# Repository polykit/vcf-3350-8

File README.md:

# Polykit VCF-3350-8

This repository contains schematics and Kicad PCB layout for an eight channel voltage controlled filter (VCF) based on the CEM3350/AS3350 state variable filter. Both frequency cutoff and resonance (Q) are voltage controllable. It offers a simoultaneous low-pass and band-pass output.

## References

https://electricdruid.net/datasheets/AS3350.pdf

http://www.synfo.nl/datasheets/CEM3350.pdf

http://www.electricdruid.net/datasheets/EMEngCEM3350.pdf

https://archive.org/details/sm_Synthesource_Issue_2

http://www.digisound80.co.uk/digisound/modules/80-16.htm

https://kg.kg/cem3350-eurorack-filter/

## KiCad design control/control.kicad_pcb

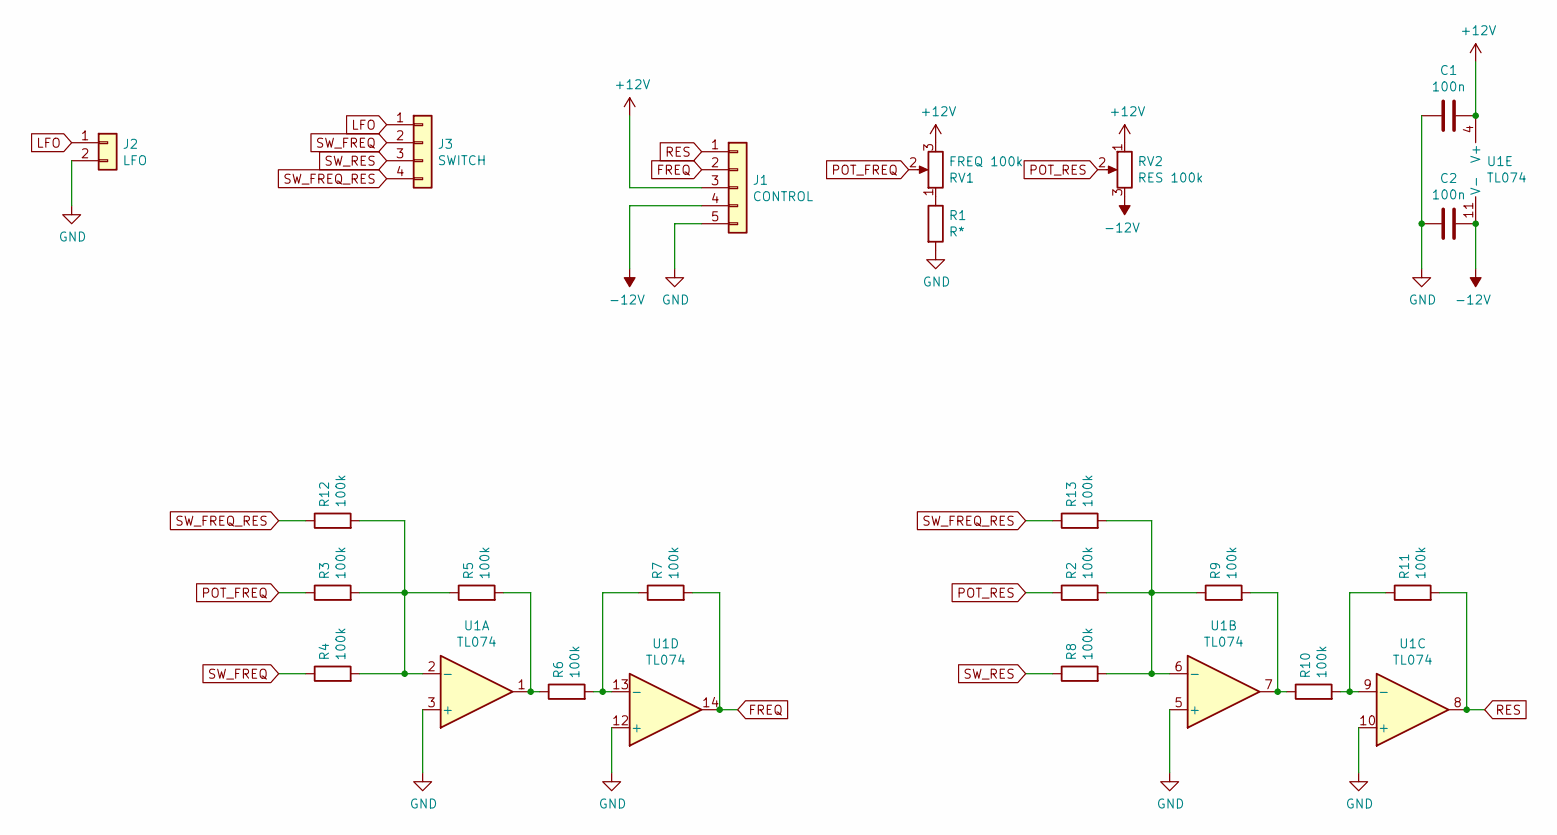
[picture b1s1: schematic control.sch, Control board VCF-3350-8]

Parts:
C1, C2: 100n; C_Disc_D3.0mm_W2.0mm_P2.50mm
J1: CONTROL; Molex_KK-254_AE-6410-05A_1x05_P2.54mm_Vertical
J2: LFO; Molex_KK-254_AE-6410-02A_1x02_P2.54mm_Vertical
J3: SWITCH; Molex_KK-254_AE-6410-04A_1x04_P2.54mm_Vertical
R1: R*; R_Axial_DIN0207_L6.3mm_D2.5mm_P10.16mm_Horizontal
R2, R3, R4, R5, R6, R7, R8, R9, R10, R11, R12, R13: 100k; R_Axial_DIN0207_L6.3mm_D2.5mm_P10.16mm_Horizontal
RV1: FREQ 100k; Potentiometer_Alpha_RD901F-40-00D_Single_Vertical
RV2: RES 100k; Potentiometer_Alpha_RD901F-40-00D_Single_Vertical
U1: TL074; DIP-14_W7.62mm_Socket_LongPads

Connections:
+12V: C1.2, J1.3, RV1.3, RV2.1, U1.4 (V+)
-12V: C2.2, J1.4, RV2.3, U1.11 (V-)
FREQ: J1.2, R7.2, U1.14
GND: C1.1, C2.1, J1.5, J2.2, R1.2, U1.3 (+), U1.5 (+), U1.10 (+), U1.12 (+)
LFO: J2.1, J3.1
unnamed: R1.1, RV1.1
unnamed: R5.2, R6.1, U1.1
unnamed: R6.2, R7.1, U1.13 (-)
unnamed: R9.2, R10.1, U1.7
unnamed: R10.2, R11.1, U1.9 (-)
unnamed: R3.2, R4.2, R5.1, R12.2, U1.2 (-)
unnamed: R2.2, R8.2, R9.1, R13.2, U1.6 (-)
POT_FREQ: R3.1, RV1.2
POT_RES: R2.1, RV2.2
RES: J1.1, R11.2, U1.8
SW_FREQ: J3.2, R4.1
SW_FREQ_RES: J3.4, R12.1, R13.1
SW_RES: J3.3, R8.1

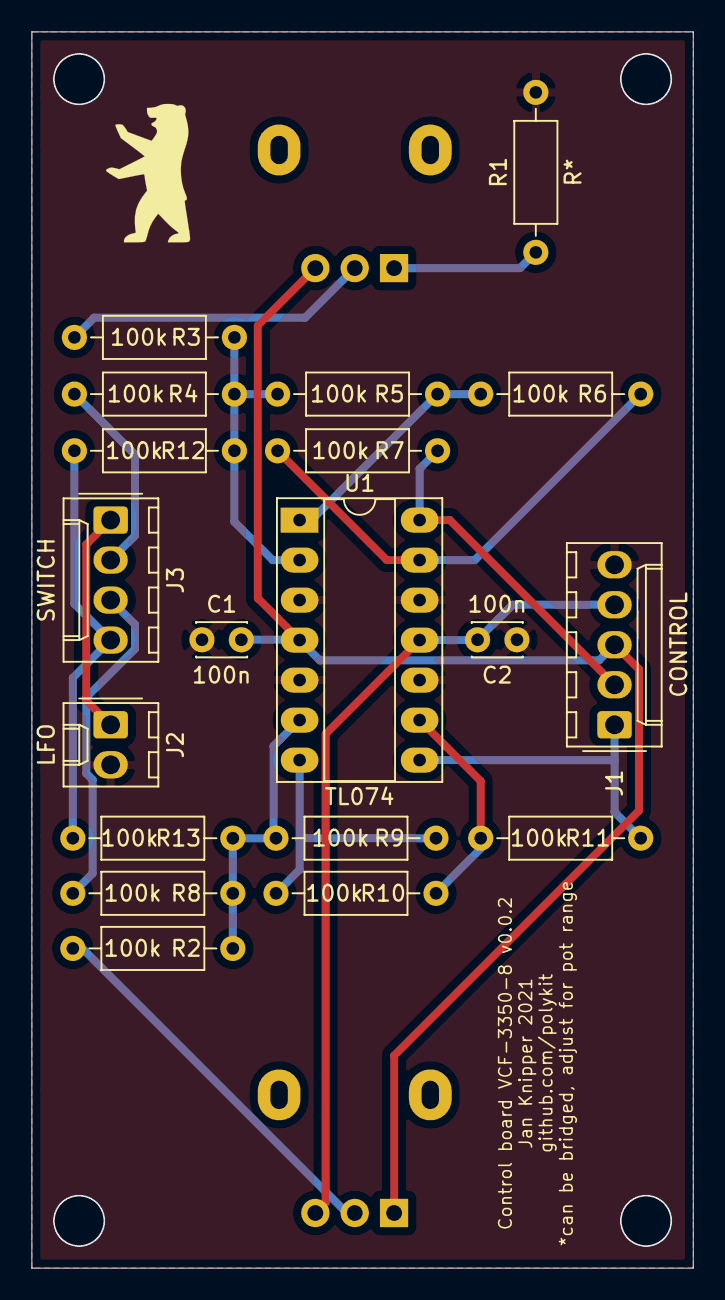
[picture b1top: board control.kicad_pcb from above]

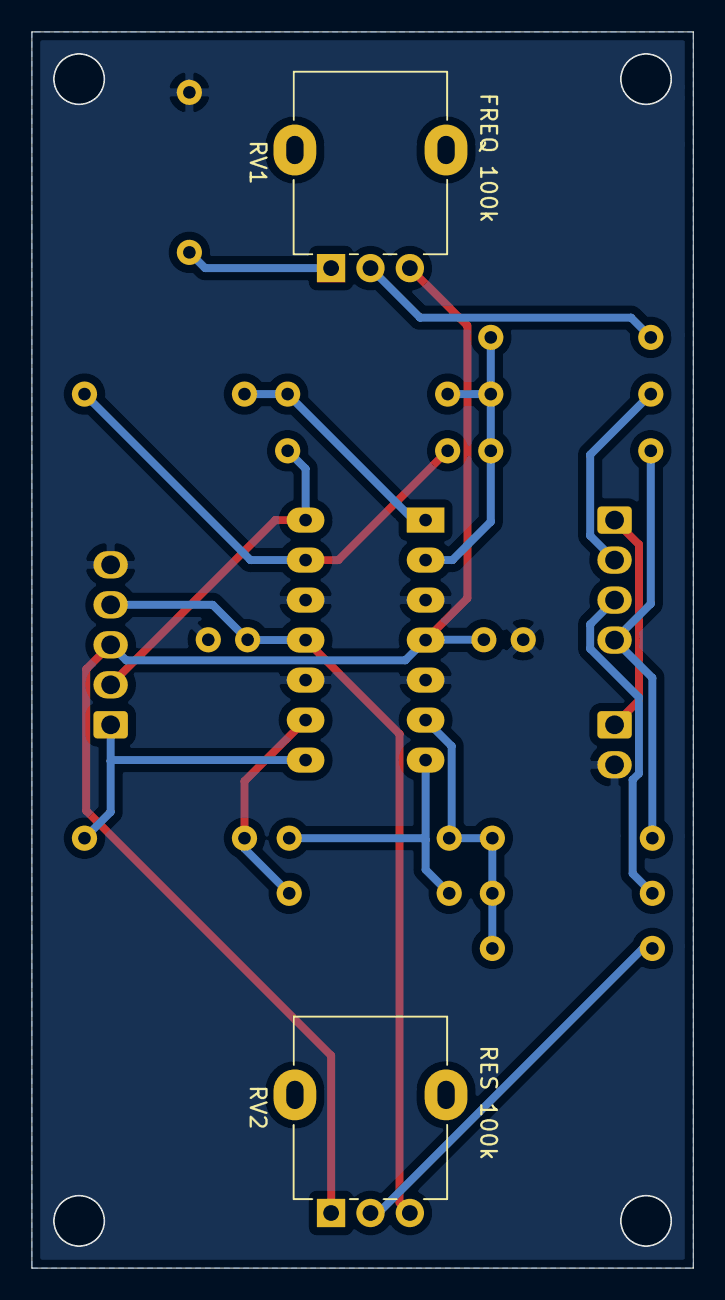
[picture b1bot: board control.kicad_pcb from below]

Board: 2 copper layers, 42.0 x 78.5 mm, 21 parts (2 on the bottom side), 18 nets.

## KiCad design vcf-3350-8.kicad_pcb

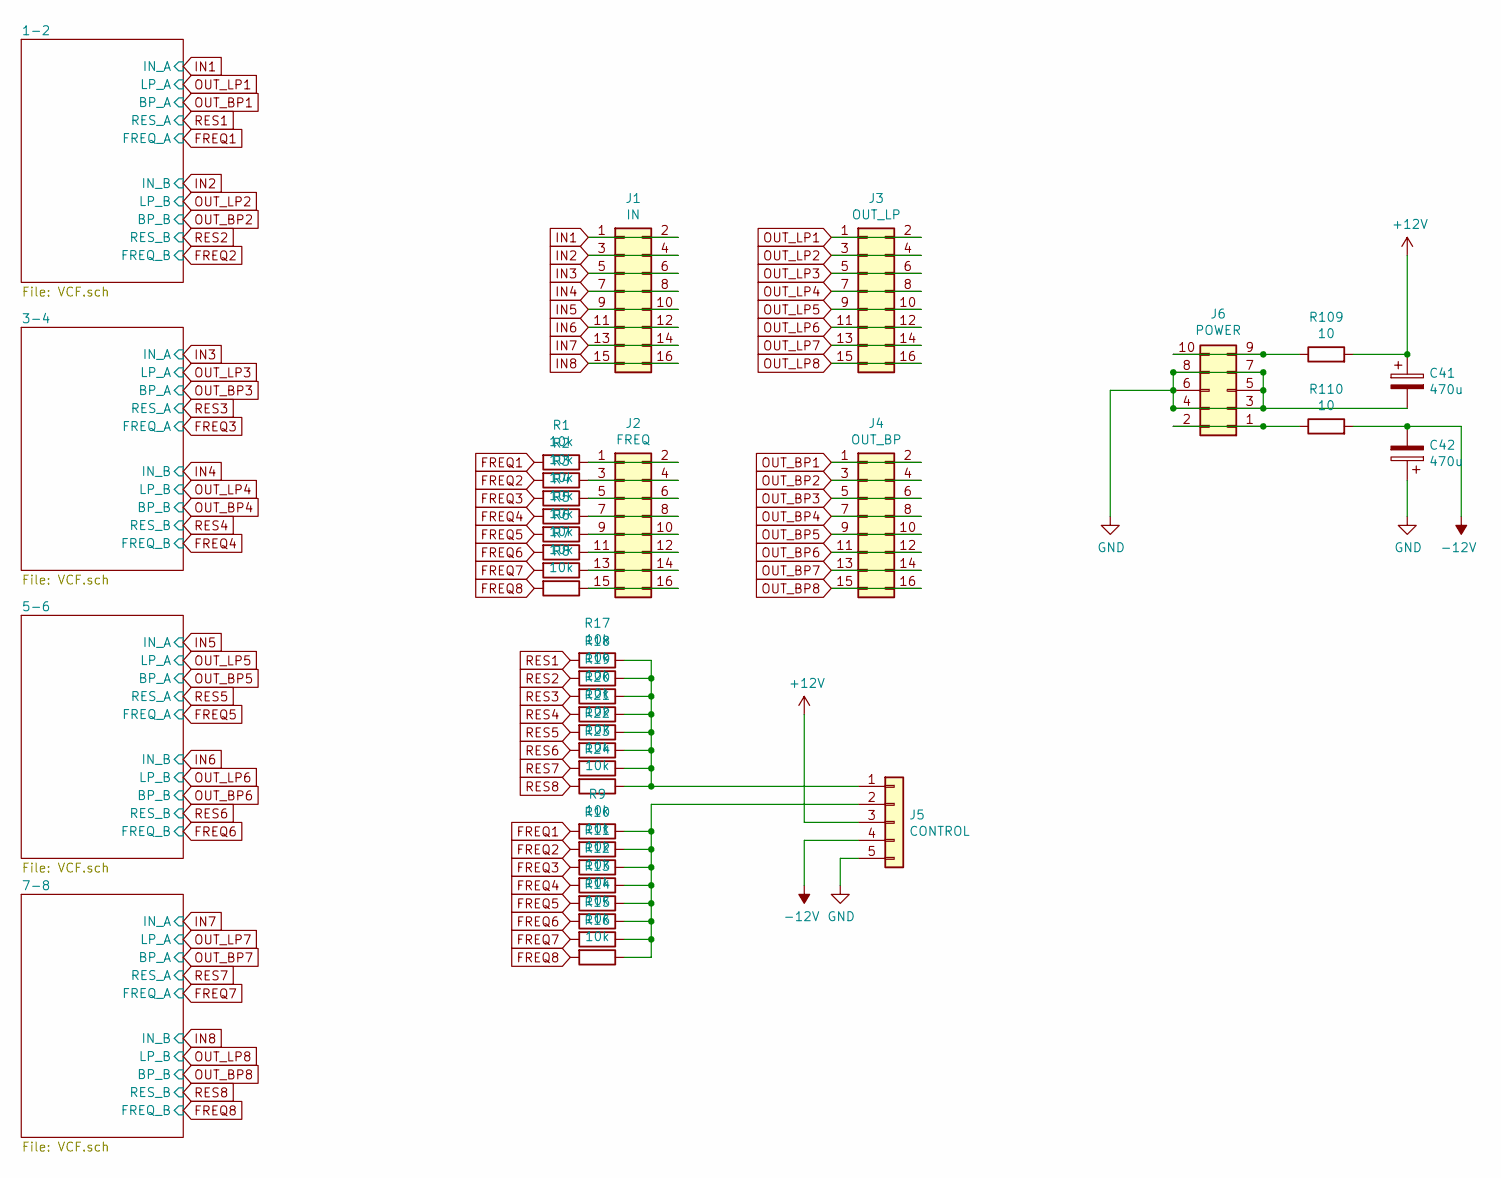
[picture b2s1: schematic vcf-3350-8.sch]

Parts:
C41, C42: 470u; CP_Radial_D8.0mm_P5.00mm
J1: IN; IDC-Header_2x08_P2.54mm_Vertical
J2: FREQ; IDC-Header_2x08_P2.54mm_Vertical
J3: OUT_LP; IDC-Header_2x08_P2.54mm_Vertical
J4: OUT_BP; IDC-Header_2x08_P2.54mm_Vertical
J5: CONTROL; Molex_KK-254_AE-6410-05A_1x05_P2.54mm_Vertical
J6: POWER; IDC-Header_2x05_P2.54mm_Vertical
R1, R2, R3, R4, R5, R6, R7, R8, R9, R10, R11, R12, R13, R14, R15, R16, R17, R18, R19, R20, R21, R22, R23, R24: 10k; R_Axial_DIN0204_L3.6mm_D1.6mm_P2.54mm_Vertical
R109, R110: 10; R_Axial_DIN0207_L6.3mm_D2.5mm_P10.16mm_Horizontal

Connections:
+12V: C41.1, J5.3, R109.2; also elsewhere on the board
-12V: C42.2, J5.4, R110.2; also elsewhere on the board
FREQ1: R1.2, R9.2; also elsewhere on the board
FREQ2: R2.2, R10.2; also elsewhere on the board
FREQ3: R3.2, R11.2; also elsewhere on the board
FREQ4: R4.2, R12.2; also elsewhere on the board
FREQ5: R5.2, R13.2; also elsewhere on the board
FREQ6: R6.2, R14.2; also elsewhere on the board
FREQ7: R7.2, R15.2; also elsewhere on the board
FREQ8: R8.2, R16.2; also elsewhere on the board
GND: C41.2, C42.1, J5.5, J6.3, J6.4, J6.5, J6.6, J6.7, J6.8; also elsewhere on the board
IN1: J1.1, J1.2; also elsewhere on the board
IN2: J1.3, J1.4; also elsewhere on the board
IN3: J1.5, J1.6; also elsewhere on the board
IN4: J1.7, J1.8; also elsewhere on the board
IN5: J1.9, J1.10; also elsewhere on the board
IN6: J1.11, J1.12; also elsewhere on the board
IN7: J1.13, J1.14; also elsewhere on the board
IN8: J1.15, J1.16; also elsewhere on the board
unnamed: J2.1, J2.2, R1.1
unnamed: J2.3, J2.4, R2.1
unnamed: J2.5, J2.6, R3.1
unnamed: J2.7, J2.8, R4.1
unnamed: J2.9, J2.10, R5.1
unnamed: J2.11, J2.12, R6.1
unnamed: J2.13, J2.14, R7.1
unnamed: J2.15, J2.16, R8.1
unnamed: J5.1, R17.1, R18.1, R19.1, R20.1, R21.1, R22.1, R23.1, R24.1
unnamed: J5.2, R9.1, R10.1, R11.1, R12.1, R13.1, R14.1, R15.1, R16.1
unnamed: J6.1, J6.2, R110.1
unnamed: J6.9, J6.10, R109.1
OUT_BP1: J4.1, J4.2; also elsewhere on the board
OUT_BP2: J4.3, J4.4; also elsewhere on the board
OUT_BP3: J4.5, J4.6; also elsewhere on the board
OUT_BP4: J4.7, J4.8; also elsewhere on the board
OUT_BP5: J4.9, J4.10; also elsewhere on the board
OUT_BP6: J4.11, J4.12; also elsewhere on the board
OUT_BP7: J4.13, J4.14; also elsewhere on the board
OUT_BP8: J4.15, J4.16; also elsewhere on the board
OUT_LP1: J3.1, J3.2; also elsewhere on the board
OUT_LP2: J3.3, J3.4; also elsewhere on the board
OUT_LP3: J3.5, J3.6; also elsewhere on the board
OUT_LP4: J3.7, J3.8; also elsewhere on the board
OUT_LP5: J3.9, J3.10; also elsewhere on the board
OUT_LP6: J3.11, J3.12; also elsewhere on the board
OUT_LP7: J3.13, J3.14; also elsewhere on the board
OUT_LP8: J3.15, J3.16; also elsewhere on the board
RES1: R17.2; also elsewhere on the board
RES2: R18.2; also elsewhere on the board
RES3: R19.2; also elsewhere on the board
RES4: R20.2; also elsewhere on the board
RES5: R21.2; also elsewhere on the board
RES6: R22.2; also elsewhere on the board
RES7: R23.2; also elsewhere on the board
RES8: R24.2; also elsewhere on the board

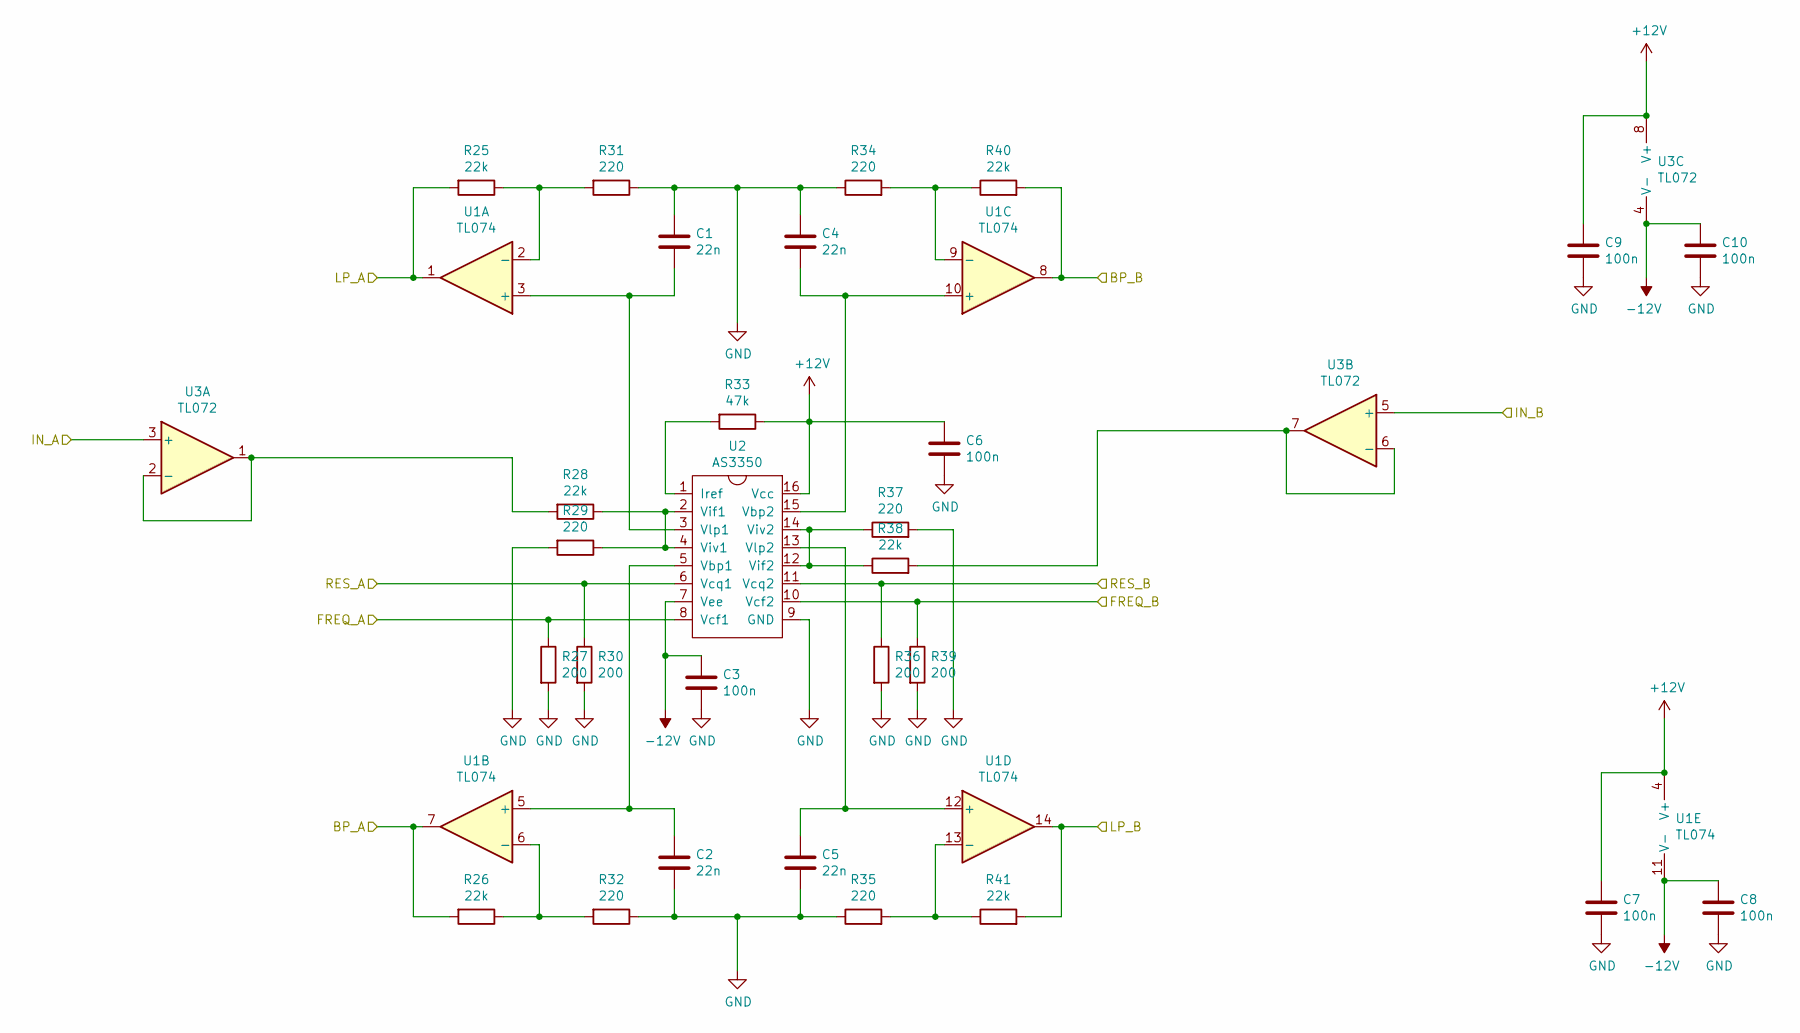
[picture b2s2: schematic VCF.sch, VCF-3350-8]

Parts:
C1, C2, C4, C5: 22n; C_Disc_D4.7mm_W2.5mm_P5.00mm
C3, C6, C7, C8, C9, C10: 100n; C_Disc_D3.4mm_W2.1mm_P2.50mm
R25, R26, R28, R38, R40, R41: 22k; R_Axial_DIN0207_L6.3mm_D2.5mm_P10.16mm_Horizontal
R27, R30, R36, R39: 200; R_Axial_DIN0207_L6.3mm_D2.5mm_P10.16mm_Horizontal
R29, R31, R32, R34, R35, R37: 220; R_Axial_DIN0207_L6.3mm_D2.5mm_P10.16mm_Horizontal
R33: 47k; R_Axial_DIN0207_L6.3mm_D2.5mm_P10.16mm_Horizontal
U1: TL074; DIP-14_W7.62mm_Socket_LongPads
U2: AS3350; DIP-16_W7.62mm_Socket_LongPads
U3: TL072; DIP-8_W7.62mm_Socket_LongPads

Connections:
+12V: C6.2, C7.2, C9.2, R33.1, U1.4 (V+), U2.16 (Vcc), U3.8 (V+); also elsewhere on the board
-12V: C3.2, C8.2, C10.2, U1.11 (V-), U2.7 (Vee), U3.4 (V-); also elsewhere on the board
FREQ1: R27.1, U2.8 (Vcf1); also elsewhere on the board
FREQ2: R39.1, U2.10 (Vcf2); also elsewhere on the board
GND: C1.1, C2.2, C3.1, C4.2, C5.1, C6.1, C7.1, C8.1, C9.1, C10.1, R27.2, R29.2, R30.2, R31.1, R32.1, R34.1, R35.1, R36.2, R37.2, R39.2, U2.9 (GND); also elsewhere on the board
IN1: U3.3 (+); also elsewhere on the board
IN2: U3.5 (+); also elsewhere on the board
unnamed: C1.2, U1.3 (+), U2.3 (Vlp1)
unnamed: C2.1, U1.5 (+), U2.5 (Vbp1)
unnamed: C4.1, U1.10 (+), U2.15 (Vbp2)
unnamed: C5.2, U1.12 (+), U2.13 (Vlp2)
unnamed: R25.1, R31.2, U1.2 (-)
unnamed: R26.1, R32.2, U1.6 (-)
unnamed: R28.1, R29.1, U2.2 (Vif1), U2.4 (Viv1)
unnamed: R28.2, U3.1, U3.2 (-)
unnamed: R33.2, U2.1 (Iref)
unnamed: R34.2, R40.1, U1.9 (-)
unnamed: R35.2, R41.1, U1.13 (-)
unnamed: R37.1, R38.1, U2.12 (Vif2), U2.14 (Viv2)
unnamed: R38.2, U3.6 (-), U3.7
OUT_BP1: R26.2, U1.7; also elsewhere on the board
OUT_BP2: R40.2, U1.8; also elsewhere on the board
OUT_LP1: R25.2, U1.1; also elsewhere on the board
OUT_LP2: R41.2, U1.14; also elsewhere on the board
RES1: R30.1, U2.6 (Vcq1); also elsewhere on the board
RES2: R36.1, U2.11 (Vcq2); also elsewhere on the board

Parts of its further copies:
C11, C12, C14, C15, C21, C22, C24, C25, C31, C32, C34, C35: 22n; C_Disc_D4.7mm_W2.5mm_P5.00mm
C13, C16, C17, C18, C19, C20, C23, C26, C27, C28, C29, C30, C33, C36, C37, C38, C39, C40: 100n; C_Disc_D3.4mm_W2.1mm_P2.50mm
R48, R49, R51, R61, R63, R64, R69, R70, R72, R82, R84, R85, R90, R91, R93, R103, R105, R106: 22k; R_Axial_DIN0207_L6.3mm_D2.5mm_P10.16mm_Horizontal
R50, R53, R59, R62, R71, R74, R80, R83, R92, R95, R101, R104: 200; R_Axial_DIN0207_L6.3mm_D2.5mm_P10.16mm_Horizontal
R52, R54, R55, R57, R58, R60, R73, R75, R76, R78, R79, R81, R94, R96, R97, R99, R100, R102: 220; R_Axial_DIN0207_L6.3mm_D2.5mm_P10.16mm_Horizontal
R56, R77, R98: 47k; R_Axial_DIN0207_L6.3mm_D2.5mm_P10.16mm_Horizontal
U4, U7, U10: TL072; DIP-8_W7.62mm_Socket_LongPads
U5, U8, U11: TL074; DIP-14_W7.62mm_Socket_LongPads
U6, U9, U12: AS3350; DIP-16_W7.62mm_Socket_LongPads

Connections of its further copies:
+12V: C16.2, C17.2, C18.2, C26.2, C27.2, C28.2, C36.2, C37.2, C38.2, R56.1, R77.1, R98.1, U4.8 (V+), U5.4 (V+), U6.16 (Vcc), U7.8 (V+), U8.4 (V+), U9.16 (Vcc), U10.8 (V+), U11.4 (V+), U12.16 (Vcc); also elsewhere on the board
-12V: C13.2, C19.2, C20.2, C23.2, C29.2, C30.2, C33.2, C39.2, C40.2, U4.4 (V-), U5.11 (V-), U6.7 (Vee), U7.4 (V-), U8.11 (V-), U9.7 (Vee), U10.4 (V-), U11.11 (V-), U12.7 (Vee); also elsewhere on the board
FREQ3: R50.1, U6.8 (Vcf1); also elsewhere on the board
FREQ4: R62.1, U6.10 (Vcf2); also elsewhere on the board
FREQ5: R71.1, U9.8 (Vcf1); also elsewhere on the board
FREQ6: R83.1, U9.10 (Vcf2); also elsewhere on the board
FREQ7: R92.1, U12.8 (Vcf1); also elsewhere on the board
FREQ8: R104.1, U12.10 (Vcf2); also elsewhere on the board
GND: C11.1, C12.2, C13.1, C14.2, C15.1, C16.1, C17.1, C18.1, C19.1, C20.1, C21.1, C22.2, C23.1, C24.2, C25.1, C26.1, C27.1, C28.1, C29.1, C30.1, C31.1, C32.2, C33.1, C34.2, C35.1, C36.1, C37.1, C38.1, C39.1, C40.1, R50.2, R52.2, R53.2, R54.1, R55.1, R57.1, R58.1, R59.2, R60.2, R62.2, R71.2, R73.2, R74.2, R75.1, R76.1, R78.1, R79.1, R80.2, R81.2, R83.2, R92.2, R94.2, R95.2, R96.1, R97.1, R99.1, R100.1, R101.2, R102.2, R104.2, U6.9 (GND), U9.9 (GND), U12.9 (GND); also elsewhere on the board
IN3: U4.3 (+); also elsewhere on the board
IN4: U4.5 (+); also elsewhere on the board
IN5: U7.3 (+); also elsewhere on the board
IN6: U7.5 (+); also elsewhere on the board
IN7: U10.3 (+); also elsewhere on the board
IN8: U10.5 (+); also elsewhere on the board
unnamed: C11.2, U5.3 (+), U6.3 (Vlp1)
unnamed: C12.1, U5.5 (+), U6.5 (Vbp1)
unnamed: C14.1, U5.10 (+), U6.15 (Vbp2)
unnamed: C15.2, U5.12 (+), U6.13 (Vlp2)
unnamed: C21.2, U8.3 (+), U9.3 (Vlp1)
unnamed: C22.1, U8.5 (+), U9.5 (Vbp1)
unnamed: C24.1, U8.10 (+), U9.15 (Vbp2)
unnamed: C25.2, U8.12 (+), U9.13 (Vlp2)
unnamed: C31.2, U11.3 (+), U12.3 (Vlp1)
unnamed: C32.1, U11.5 (+), U12.5 (Vbp1)
unnamed: C34.1, U11.10 (+), U12.15 (Vbp2)
unnamed: C35.2, U11.12 (+), U12.13 (Vlp2)
unnamed: R48.1, R54.2, U5.2 (-)
unnamed: R49.1, R55.2, U5.6 (-)
unnamed: R51.1, R52.1, U6.2 (Vif1), U6.4 (Viv1)
unnamed: R51.2, U4.1, U4.2 (-)
unnamed: R56.2, U6.1 (Iref)
unnamed: R57.2, R63.1, U5.9 (-)
unnamed: R58.2, R64.1, U5.13 (-)
unnamed: R60.1, R61.1, U6.12 (Vif2), U6.14 (Viv2)
unnamed: R61.2, U4.6 (-), U4.7
unnamed: R69.1, R75.2, U8.2 (-)
unnamed: R70.1, R76.2, U8.6 (-)
unnamed: R72.1, R73.1, U9.2 (Vif1), U9.4 (Viv1)
unnamed: R72.2, U7.1, U7.2 (-)
unnamed: R77.2, U9.1 (Iref)
unnamed: R78.2, R84.1, U8.9 (-)
unnamed: R79.2, R85.1, U8.13 (-)
unnamed: R81.1, R82.1, U9.12 (Vif2), U9.14 (Viv2)
unnamed: R82.2, U7.6 (-), U7.7
unnamed: R90.1, R96.2, U11.2 (-)
unnamed: R91.1, R97.2, U11.6 (-)
unnamed: R93.1, R94.1, U12.2 (Vif1), U12.4 (Viv1)
unnamed: R93.2, U10.1, U10.2 (-)
unnamed: R98.2, U12.1 (Iref)
unnamed: R100.2, R106.1, U11.13 (-)
unnamed: R102.1, R103.1, U12.12 (Vif2), U12.14 (Viv2)
unnamed: R103.2, U10.6 (-), U10.7
unnamed: R99.2, R105.1, U11.9 (-)
OUT_BP3: R49.2, U5.7; also elsewhere on the board
OUT_BP4: R63.2, U5.8; also elsewhere on the board
OUT_BP5: R70.2, U8.7; also elsewhere on the board
OUT_BP6: R84.2, U8.8; also elsewhere on the board
OUT_BP7: R91.2, U11.7; also elsewhere on the board
OUT_BP8: R105.2, U11.8; also elsewhere on the board
OUT_LP3: R48.2, U5.1; also elsewhere on the board
OUT_LP4: R64.2, U5.14; also elsewhere on the board
OUT_LP5: R69.2, U8.1; also elsewhere on the board
OUT_LP6: R85.2, U8.14; also elsewhere on the board
OUT_LP7: R90.2, U11.1; also elsewhere on the board
OUT_LP8: R106.2, U11.14; also elsewhere on the board
RES3: R53.1, U6.6 (Vcq1); also elsewhere on the board
RES4: R59.1, U6.11 (Vcq2); also elsewhere on the board
RES5: R74.1, U9.6 (Vcq1); also elsewhere on the board
RES6: R80.1, U9.11 (Vcq2); also elsewhere on the board
RES7: R95.1, U12.6 (Vcq1); also elsewhere on the board
RES8: R101.1, U12.11 (Vcq2); also elsewhere on the board

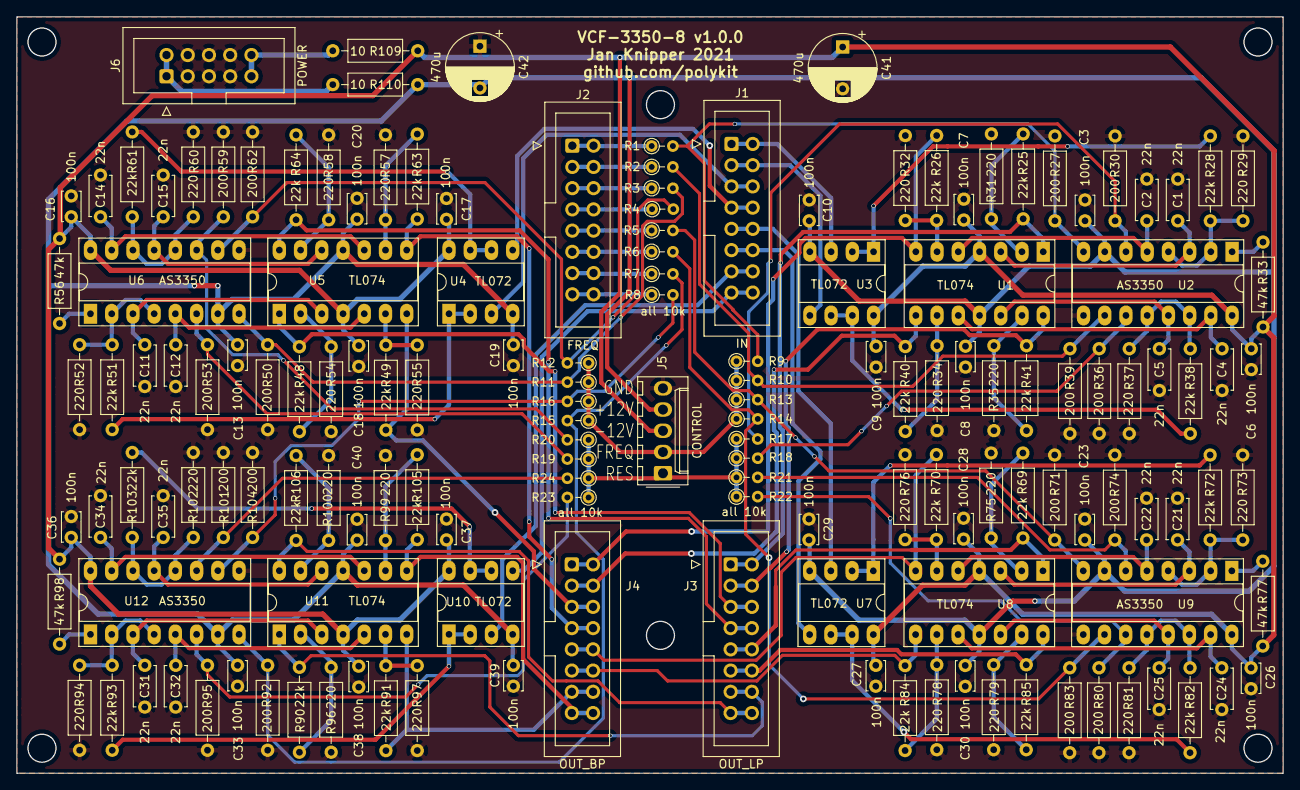
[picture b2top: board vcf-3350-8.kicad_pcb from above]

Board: 2 copper layers, 151.5 x 90.5 mm, 154 parts (0 on the bottom side), 107 nets.

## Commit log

2021-08-15 Initial import
2021-10-08 Update control board
